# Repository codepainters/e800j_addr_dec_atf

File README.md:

# PROM replacement for Elwro 800 Junior - ATF1502ASL SMD variant

Elwro 800 Junior uses two `SN74S474` 512x8 PROMs as IO and memory address decoders. These PROMs are increasingly difficult to obtain (and program), this project provides a plug-in replacement for both address decoders based on `ATF1502ASL` CPLD in `TQFP-44` package.

Note: there is [another version](https://github.com/codepainters/e800j_addr_dec_gal/) using `GAL16V8` in `DIL-20`. 

Hardware files:

* [pcb](pcb) - schematic/PCB project in KiCAD 8 format
* PDF schematics - [color](pdf/addr_dec.pdf) and [black&white](pdf/addr_dec_bw.pdf)
* [interactive BOM](addr_dec_atf_ibom.html) file (you have to download it and open locally)
* Gerber files (in a [jlcpcb](https://jlcpcb.com/)-compatible ZIP format):
  * [addr\_dec\_atf.zip](gerbers/addr_dec_atf.zip) - single PCB
  * [addr\_dec\_atf\_panel.zip](gerbers/addr_dec_atf_panel.zip) - two PCBs panelized

For bitstream files and programming instructions go to [bitstreams](bitstreams).

Under [src](src) you can find Quartus projects for I/O and MEM decoders (look there for details).

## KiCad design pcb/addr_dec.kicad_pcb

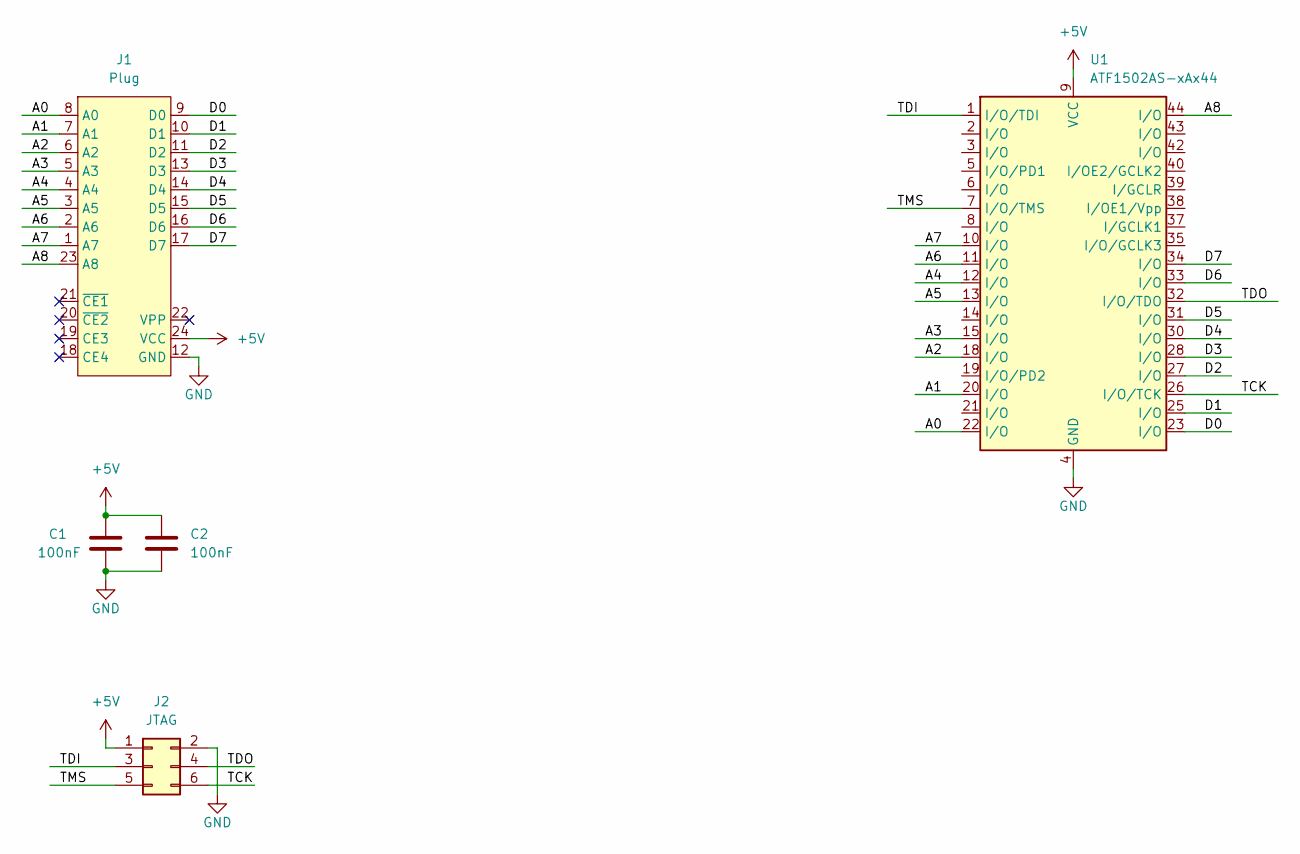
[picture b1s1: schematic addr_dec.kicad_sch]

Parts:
C1, C2: 100nF; C_0603_1608Metric_Pad1.08x0.95mm_HandSolder
J1: Plug; DIP-24_W15.24mm
J2: JTAG; PinHeader_2x03_P2.00mm_Vertical
U1: ATF1502AS-xAx44; TQFP-44_10x10mm_P0.8mm

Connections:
+5V: C1.1, C2.1, J1.24 (VCC), J2.1, U1.9 (VCC), U1.17 (VCC), U1.29 (VCC), U1.41 (VCC)
/A0: J1.8 (A0), U1.22 (I/O)
/A1: J1.7 (A1), U1.20 (I/O)
/A2: J1.6 (A2), U1.18 (I/O)
/A3: J1.5 (A3), U1.15 (I/O)
/A4: J1.4 (A4), U1.12 (I/O)
/A5: J1.3 (A5), U1.13 (I/O)
/A6: J1.2 (A6), U1.11 (I/O)
/A7: J1.1 (A7), U1.10 (I/O)
/A8: J1.23 (A8), U1.44 (I/O)
/D0: J1.9 (D0), U1.23 (I/O)
/D1: J1.10 (D1), U1.25 (I/O)
/D2: J1.11 (D2), U1.27 (I/O)
/D3: J1.13 (D3), U1.28 (I/O)
/D4: J1.14 (D4), U1.30 (I/O)
/D5: J1.15 (D5), U1.31 (I/O)
/D6: J1.16 (D6), U1.33 (I/O)
/D7: J1.17 (D7), U1.34 (I/O)
/TCK: J2.6, U1.26 (I/O/TCK)
/TDI: J2.3, U1.1 (I/O/TDI)
/TDO: J2.4, U1.32 (I/O/TDO)
/TMS: J2.5, U1.7 (I/O/TMS)
GND: C1.2, C2.2, J1.12 (GND), J2.2, U1.4 (GND), U1.16 (GND), U1.24 (GND), U1.36 (GND)

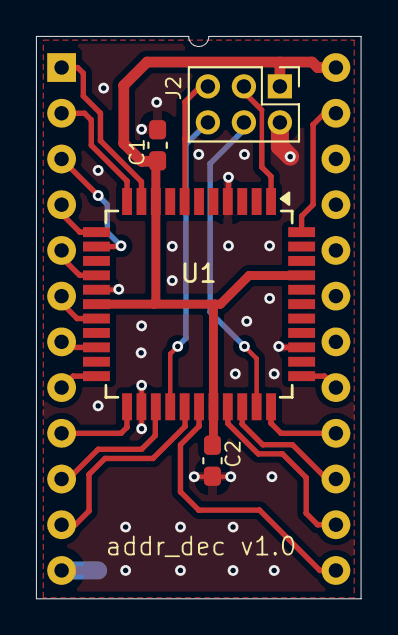
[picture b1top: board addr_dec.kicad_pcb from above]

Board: 2 copper layers, 18.0 x 31.2 mm, 5 parts (0 on the bottom side), 23 nets.

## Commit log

2025-02-10 Initial import
2025-02-10 Added a PCB picture
2025-02-10 openocd wrapper script
2025-02-11 Added gerber files
2025-02-11 Schematic in PDF format
2025-02-11 Added iBOM, updated README
2025-02-11 Renamed pdfs dir for consistency
2025-02-11 Bitstreams cleaned up, added programming info.
2025-02-11 Source files README
2025-02-11 Update README.md - fix WineHQ link.
